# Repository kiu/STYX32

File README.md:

# STYX32
STYX32 - STM32 In-Circuit-Programming

# Connectors
STYX32 puts every programming and debug connection on the same pinout. Target boards use one of
these headers; pins 1, 3 and 5 are always 3V3, RESET (GND on D) and GND.

| Marking | Header | 1 | 2 | 3 | 4 | 5 | 6 | 7 | 8 | 9 | 10 |
|---|---|---|---|---|---|---|---|---|---|---|---|
| S32A | 2x3 serial | 3V3 | TX | RESET | RX | GND | BOOT0 | | | | |
| S32B1 | 2x3 SWD + serial | 3V3 | SWDIO | RESET | SWDCLK | GND | TX | | | | |
| S32B2 | 2x3 SWD + SWO | 3V3 | SWDIO | RESET | SWDCLK | GND | SWO | | | | |
| S32C | 2x4 SWD + SWO + serial | 3V3 | SWDIO | RESET | SWDCLK | GND | SWO | TX | RX | | |
| S32D | 2x5 ARM Cortex debug | 3V3 | SWDIO | GND | SWDCLK | GND | SWO | KEY | TDI | GND | RESET |

TX and RX are seen from the target: TX is the target's output.

## KiCad library
[lib/](lib/) has a symbol and a footprint for every connector in four variants (2.54 mm and
1.27 mm pitch, SMD and THT), named `STYX32_<connector>_2x<rows>_<pitch>_<SMD|THT>`. The symbols
look like KiCad's generic 2-row connectors, link their footprint and carry the LCSC part number.
The footprints show the marking (e.g. S32B2), a pin 1 mark and the key notch on the silkscreen,
and the pin names on F.Fab.

Every connector also comes as a card edge, `STYX32_<connector>_2x<rows>_P2.54mm_Edge`: gold
fingers on both sides of a 1.6 mm board (odd pins on top, even pins below them) that plug into a
2.54 mm edge slot socket, e.g. WingTAT ED06BGFBK / ED08BGFBK / ED10BGFBK (LCSC C5173287 / C5173288 /
C5173289, in the symbol's `Mate` field). The socket has no key: a triangle on top and a square on
the bottom mark the pin 1 end. The footprint brings the card outline on Edge.Cuts; join its two
ends to your board edge, straight across for a card sticking out of the board, or along the notch
guide on User.Drawings for a card cut into the board. The plugged socket is drawn on User.Drawings
beyond the card edge. Card edges are not part of the BOM; ENIG is fine, a bevelled edge plugs in
more easily.

The [template](lib/template/) schematic has every connector wired to global labels
(`STM_SWDIO`, `STM_SWDCLK`, `STM_SWO`, `STM_RESET`, `STM_TX`, `STM_RX`, `STM_BOOT0`, `STM_TDI`),
`+3V3` and `GND`: copy a connector with its labels into your own schematic.

1. Add `lib/STYX32.kicad_sym` and `lib/STYX32.pretty` to your symbol and footprint library tables
   (nickname `STYX32`).
2. For the 1.27 mm 3D models, set the path variable `STYX32_LIB` to the `lib` folder
   (Preferences > Configure Paths).

The whole library is generated by [lib/tools/](lib/tools/): `gen_symbols.py` (any Python),
`gen_footprints.py` (KiCad's Python) and `make_3d.py` (FreeCAD) for the 1.27 mm models.

# Files
- [main](REV_A/main/): KiCad schematic, board and gerbers
- [template](lib/template/): KiCad project showing every connector of the library
- [lib](lib/): KiCad symbol and footprint library for the connectors
- [BOM](REV_A/STYX32-bom.ods): Bill of materials [(PDF)](REV_A/STYX32-bom.pdf)
- [firmware](firmware/): STM32CubeIDE project

# Links
- [IDCto127](https://github.com/kiu/IDCto127)

# License
This project is licensed under the Creative Commons Attribution-NonCommercial 3.0 Unported (CC BY-NC 3.0) license.

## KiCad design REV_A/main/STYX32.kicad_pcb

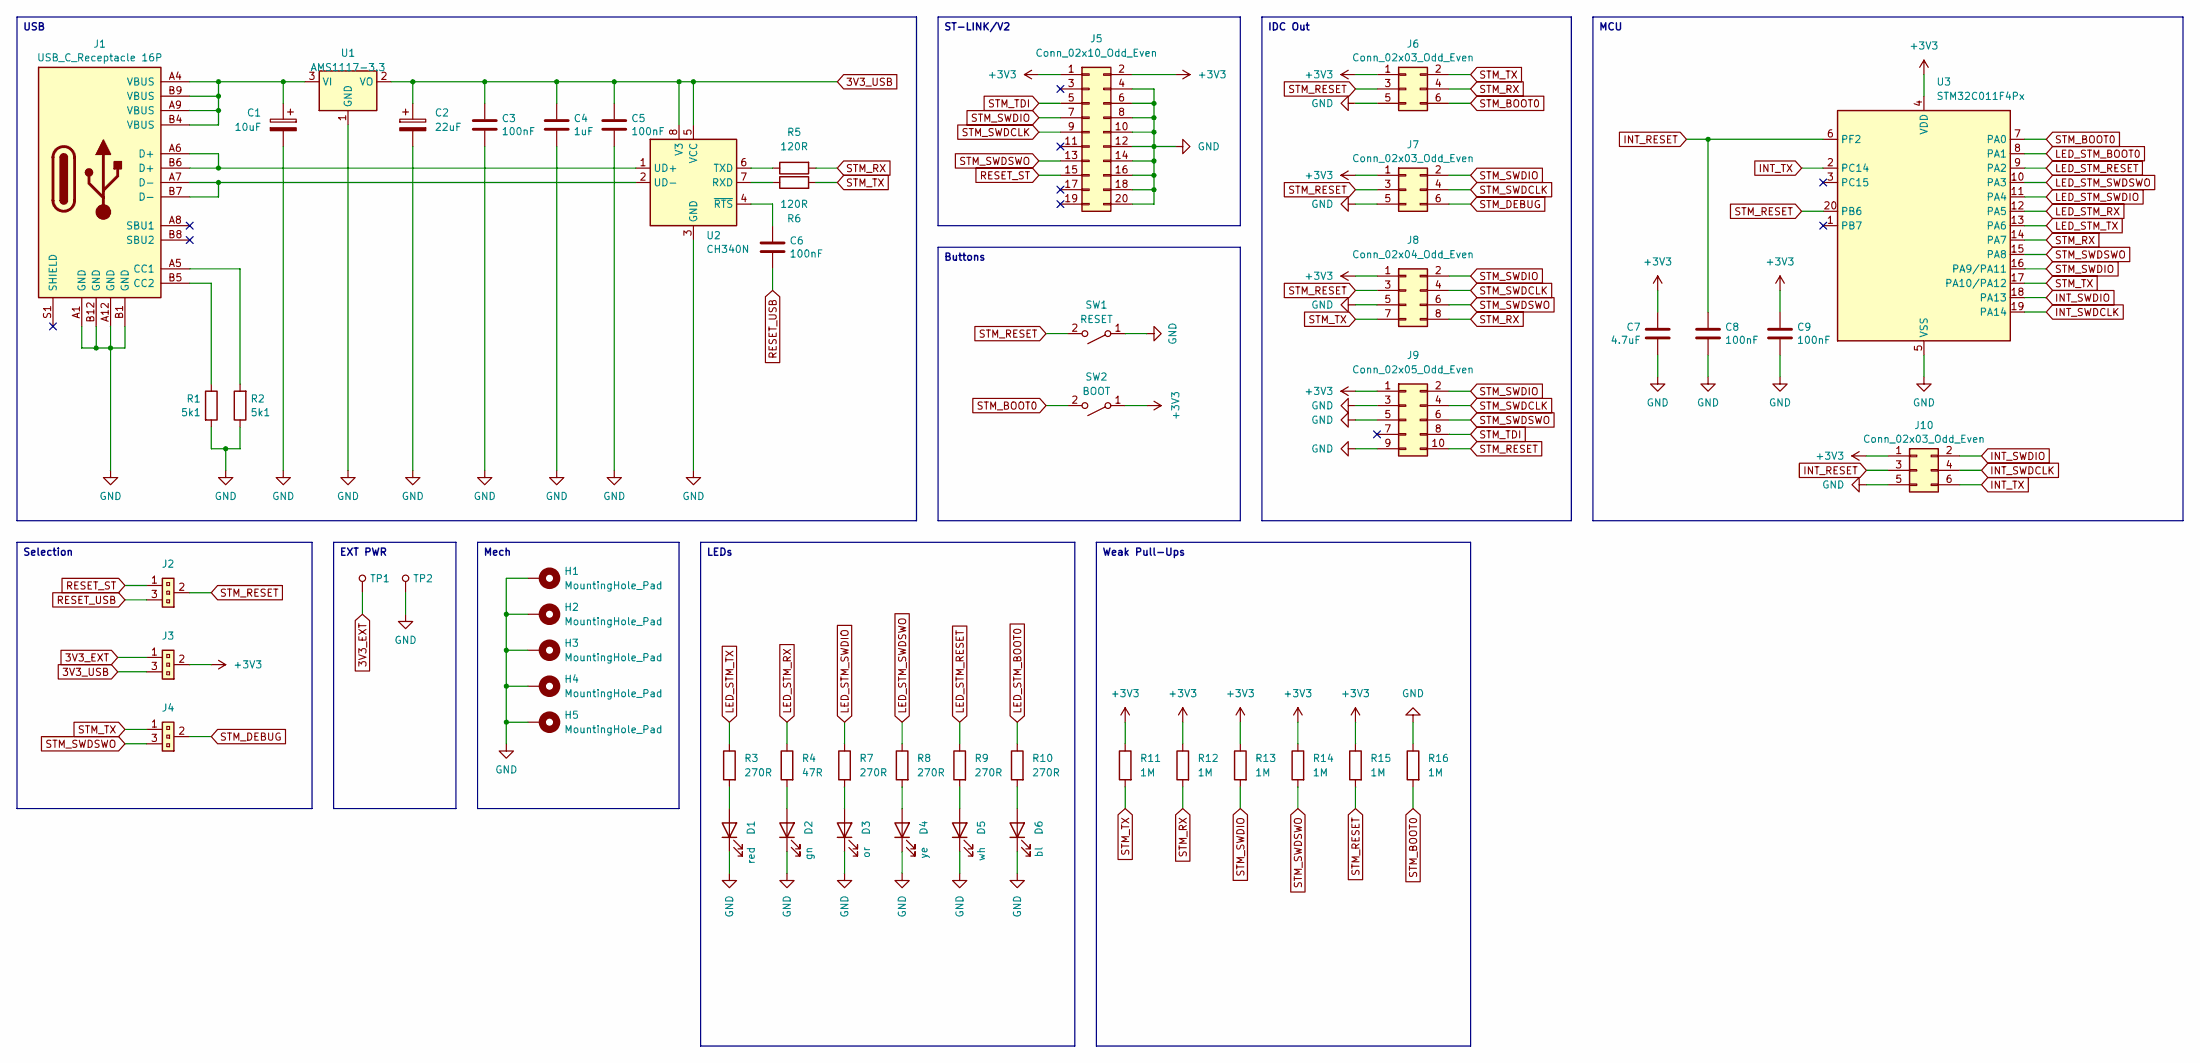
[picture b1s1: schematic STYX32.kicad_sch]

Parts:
C1: 10uF; CP_EIA-3216-18_Kemet-A; LCSC C119052
C2: 22uF; CP_EIA-3216-18_Kemet-A; LCSC C122643
C3, C5, C6, C8, C9: 100nF; C_0805_2012Metric; LCSC C49678
C4: 1uF; C_0805_2012Metric; LCSC C28323
C7: 4.7uF; C_0805_2012Metric; LCSC C98192
D1: red; LED_1206_TOGIALED TJ-S3216SWETNPLC2_REVERSE; LCSC C7545697
D2: gn; LED_1206_TOGIALED TJ-S3216SWETNPLC2_REVERSE; LCSC C7545703
D3: or; LED_1206_TOGIALED TJ-S3216SWETNPLC2_REVERSE; LCSC C7545709
D4: ye; LED_1206_TOGIALED TJ-S3216SWETNPLC2_REVERSE; LCSC C7545699
D5: wh; LED_1206_TOGIALED TJ-S3216SWETNPLC2_REVERSE; LCSC C7545707
D6: bl; LED_1206_TOGIALED TJ-S3216SWETNPLC2_REVERSE; LCSC C7545701
H1, H2, H3, H4, H5: MountingHole_Pad; MountingHole_3.2mm_M3_DIN965_Pad
J1: USB_C_Receptacle 16P; USB_C_Receptacle_Korean_Hroparts_Elec_TYPE-C-31-M-12; LCSC C165948
J2, J3, J4: 1x03_Jumper; PinHeader_1x03_P2.54mm_Vertical; LCSC C6332196
J5: Conn_02x10_Odd_Even; IDC-Header_2x10_P2.54mm_Vertical; LCSC C93700
J6, J7: Conn_02x03_Odd_Even; IDC-Header_2x03_P2.54mm_Vertical; LCSC C492441
J8: Conn_02x04_Odd_Even; IDC-Header_2x04_P2.54mm_Vertical; LCSC C17179451
J9: Conn_02x05_Odd_Even; IDC-Header_2x05_P2.54mm_Vertical; LCSC C5665
J10: Conn_02x03_Odd_Even; IDC-Header_2x03_P1.27mm_Vertical_SMD; LCSC C42372553
R1, R2: 5k1; R_0805_2012Metric; LCSC C27834
R3, R7, R8, R9, R10: 270R; R_0805_2012Metric; LCSC C2907313
R4: 47R; R_0805_2012Metric; LCSC C2907331
R5, R6: 120R; R_0805_2012Metric; LCSC C17437
R11, R12, R13, R14, R15, R16: 1M; R_0805_2012Metric; LCSC C2907302
SW1: RESET; SW_PUSH-12mm; LCSC C2843931
SW2: BOOT; SW_PUSH-12mm; LCSC C2843931
TP1, TP2: 5011; TestPoint_Keystone_5010-5014_Multipurpose; MPN 5011; Digi-Key_PN 36-5011-ND
U1: AMS1117-3.3; SOT-223-3_TabPin2; LCSC C347222
U2: CH340N; SOP-8_3.9x4.9mm_P1.27mm; LCSC C2977777
U3: STM32C011F4Px; TSSOP-20_4.4x6.5mm_P0.65mm; LCSC C7373263

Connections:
3V3_EXT: J3.1, TP1.1
3V3_USB: C2.1, C3.1, C4.1, C5.1, J3.3, U1.2 (VO), U2.5 (VCC), U2.8 (V3)
+3V3: C7.1, C9.1, J3.2, J5.1, J5.2, J6.1, J7.1, J8.1, J9.1, J10.1, R11.1, R12.1, R13.1, R14.1, R15.1, SW2.1 (A), U3.4 (VDD)
GND: C1.2, C2.2, C3.2, C4.2, C5.2, C7.2, C8.2, C9.2, D1.1 (K), D2.1 (K), D3.1 (K), D4.1 (K), D5.1 (K), D6.1 (K), H1.1, H2.1, H3.1, H4.1, H5.1, J1.A1 (GND), J1.A12 (GND), J1.B1 (GND), J1.B12 (GND), J5.4, J5.6, J5.8, J5.10, J5.12, J5.14, J5.16, J5.18, J5.20, J6.5, J7.5, J8.5, J9.3, J9.5, J9.9, J10.5, R1.2, R2.1, R16.1, SW1.1 (A), TP2.1, U1.1 (GND), U2.3 (GND), U3.5 (VSS)
INT_RESET: C8.1, J10.3, U3.6 (PF2)
INT_SWDCLK: J10.4, U3.19 (PA14)
INT_SWDIO: J10.2, U3.18 (PA13)
INT_TX: J10.6, U3.2 (PC14)
LED_STM_BOOT0: R10.1, U3.8 (PA1)
LED_STM_RESET: R9.1, U3.9 (PA2)
LED_STM_RX: R4.1, U3.12 (PA5)
LED_STM_SWDIO: R7.1, U3.11 (PA4)
LED_STM_SWDSWO: R8.1, U3.10 (PA3)
LED_STM_TX: R3.1, U3.13 (PA6)
unnamed: D1.2 (A), R3.2
unnamed: D2.2 (A), R4.2
unnamed: D3.2 (A), R7.2
unnamed: D4.2 (A), R8.2
unnamed: D5.2 (A), R9.2
unnamed: D6.2 (A), R10.2
unnamed: J1.A5 (CC1), R2.2
unnamed: J1.B5 (CC2), R1.1
unnamed: C1.1, J1.A4 (VBUS), J1.A9 (VBUS), J1.B4 (VBUS), J1.B9 (VBUS), U1.3 (VI)
unnamed: R6.1, U2.7 (RXD)
unnamed: R5.1, U2.6 (TXD)
unnamed: J1.A6 (D+), J1.B6 (D+), U2.1 (UD+)
unnamed: J1.A7 (D-), J1.B7 (D-), U2.2 (UD-)
unnamed: C6.1, U2.4 (~RTS)
RESET_ST: J2.1, J5.15
RESET_USB: C6.2, J2.3
STM_BOOT0: J6.6, R16.2, SW2.2 (B), U3.7 (PA0)
STM_DEBUG: J4.2, J7.6
STM_RESET: J2.2, J6.3, J7.3, J8.3, J9.10, R15.2, SW1.2 (B), U3.20 (PB6)
STM_RX: J6.4, J8.8, R5.2, R12.2, U3.14 (PA7)
STM_SWDCLK: J5.9, J7.4, J8.4, J9.4
STM_SWDIO: J5.7, J7.2, J8.2, J9.2, R13.2, U3.16 (PA9/PA11)
STM_SWDSWO: J4.3, J5.13, J8.6, J9.6, R14.2, U3.15 (PA8)
STM_TDI: J5.5, J9.8
STM_TX: J4.1, J6.2, J8.7, R6.2, R11.2, U3.17 (PA10/PA12)

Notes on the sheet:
Weak Pull-Ups
ST-LINK/V2
Mech
Buttons
EXT PWR
LEDs
USB
IDC Out
MCU
Selection

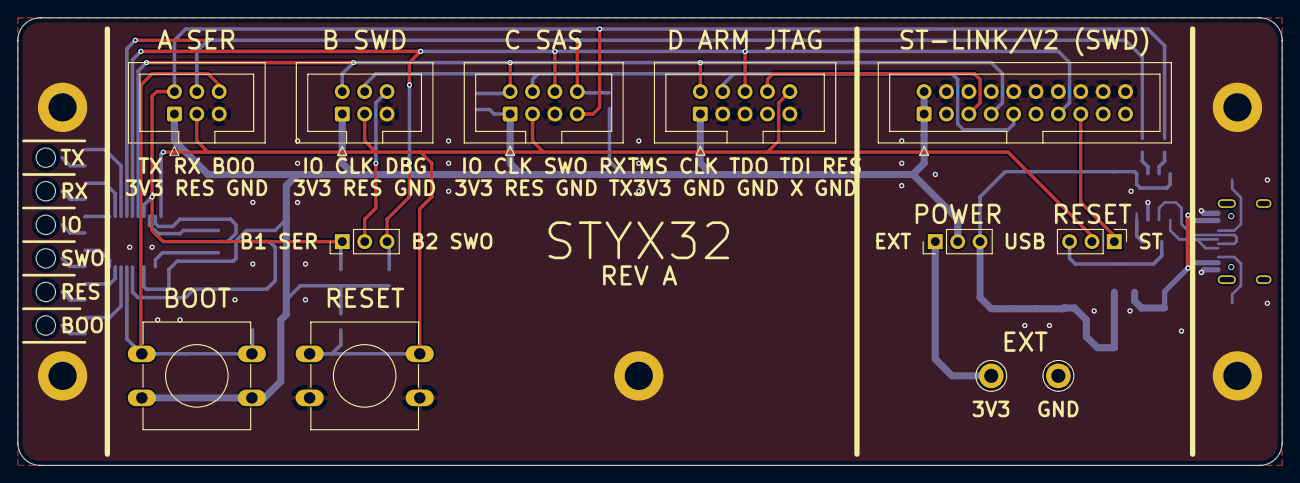
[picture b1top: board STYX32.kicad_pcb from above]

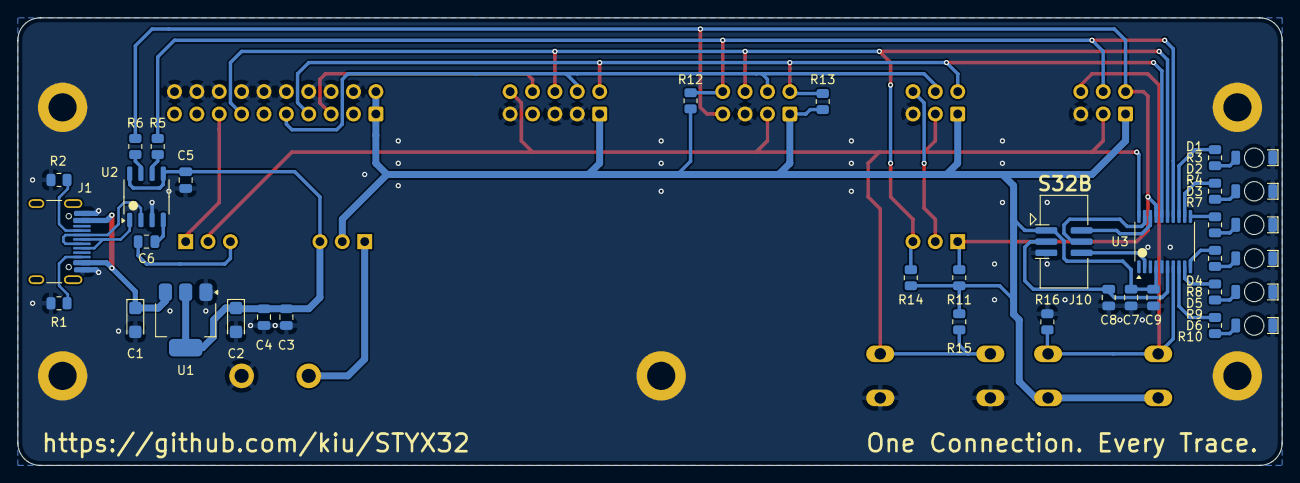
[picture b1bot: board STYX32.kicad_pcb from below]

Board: 2 copper layers, 143.5 x 50.8 mm, 53 parts (36 on the bottom side), 39 nets.

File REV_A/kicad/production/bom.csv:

Designator,Footprint,Quantity,Value,LCSC Part #
C1,CP_EIA-3216-18_Kemet-A,1,10uF,C119052
C2,CP_EIA-3216-18_Kemet-A,1,22uF,C122643
"C3, C5, C6, C8, C9",0805,5,100nF,C49678
C4,0805,1,1uF,C28323
C7,0805,1,4.7uF,C98192
D1,LED_1206_TOGIALED TJ-S3216SWETNPLC2_REVERSE,1,red,C7545697
D2,LED_1206_TOGIALED TJ-S3216SWETNPLC2_REVERSE,1,gn,C7545703
D3,LED_1206_TOGIALED TJ-S3216SWETNPLC2_REVERSE,1,or,C7545709
D4,LED_1206_TOGIALED TJ-S3216SWETNPLC2_REVERSE,1,ye,C7545699
D5,LED_1206_TOGIALED TJ-S3216SWETNPLC2_REVERSE,1,wh,C7545707
D6,LED_1206_TOGIALED TJ-S3216SWETNPLC2_REVERSE,1,bl,C7545701
J1,USB_C_Receptacle_Korean_Hroparts_Elec_TYPE-C-31-M-12,1,USB_C_Receptacle 16P,C165948
J10,IDC-Header_2x03_P1.27mm_Vertical_SMD,1,Conn_02x03_Odd_Even,C42372553
"J2, J3, J4",PinHeader_1x03_P2.54mm_Vertical,3,1x03_Jumper,C6332196
J5,IDC-Header_2x10_P2.54mm_Vertical,1,Conn_02x10_Odd_Even,C93700
"J6, J7",IDC-Header_2x03_P2.54mm_Vertical,2,Conn_02x03_Odd_Even,C492441
J8,IDC-Header_2x04_P2.54mm_Vertical,1,Conn_02x04_Odd_Even,C17179451
J9,IDC-Header_2x05_P2.54mm_Vertical,1,Conn_02x05_Odd_Even,C5665
"R1, R2",0805,2,5k1,C27834
"R10, R3, R7, R8, R9",0805,5,270R,C2907313
"R11, R12, R13, R14, R15, R16",0805,6,1M,C2907302
R4,0805,1,47R,C2907331
"R5, R6",0805,2,120R,C17437
SW1,SW_PUSH-12mm,1,RESET,C2843931
SW2,SW_PUSH-12mm,1,BOOT,C2843931
TP1,TestPoint_Keystone_5010-5014_Multipurpose,1,5011,C2906765
TP2,TestPoint_Keystone_5010-5014_Multipurpose,1,5011,C238127
U1,SOT-223-3_TabPin2,1,AMS1117-3.3,C347222
U2,SOP-8_3.9x4.9mm_P1.27mm,1,CH340N,C2977777
U3,TSSOP-20_4.4x6.5mm_P0.65mm,1,STM32C011F4Px,C7373263

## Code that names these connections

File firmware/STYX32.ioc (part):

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Mcu.Name=STM32C011F(4-6)Px
Mcu.Package=TSSOP20
Mcu.UserName=STM32C011F4Px
PA0.GPIOParameters=GPIO_Label
PA0.GPIO_Label=STM_BOOT0
PA0.Signal=GPXTI0
PA1.GPIOParameters=GPIO_Label
PA1.GPIO_Label=LED_STM_BOOT0
PA1.Signal=GPIO_Output
PA11\ [PA9].GPIOParameters=GPIO_Label,GPIO_ModeDefaultEXTI
PA11\ [PA9].GPIO_Label=STM_SWDIO
PA11\ [PA9].GPIO_ModeDefaultEXTI=GPIO_MODE_IT_FALLING
PA11\ [PA9].Signal=GPXTI11
PA12\ [PA10].GPIOParameters=GPIO_PuPd,GPIO_Label,GPIO_ModeDefaultEXTI
PA12\ [PA10].GPIO_Label=STM_TX
PA12\ [PA10].GPIO_ModeDefaultEXTI=GPIO_MODE_IT_FALLING
PA12\ [PA10].GPIO_PuPd=GPIO_PULLUP
PA12\ [PA10].Signal=GPXTI12
PA13.Mode=Serial_Wire
PA13.Signal=DEBUG_SWDIO
PA14-BOOT0.Mode=Serial_Wire
PA14-BOOT0.Signal=DEBUG_SWCLK
PA2.GPIOParameters=GPIO_Label
PA2.GPIO_Label=LED_STM_RESET
PA2.Signal=GPIO_Output
PA3.GPIOParameters=GPIO_Label
PA3.GPIO_Label=LED_STM_SWDSWO
PA3.Signal=GPIO_Output
PA4.GPIOParameters=GPIO_Label
PA4.GPIO_Label=LED_STM_SWDIO
PA4.Signal=GPIO_Output
PA5.GPIOParameters=GPIO_Label
PA5.GPIO_Label=LED_STM_RX
PA5.Signal=GPIO_Output
PA6.GPIOParameters=GPIO_Label
PA6.GPIO_Label=LED_STM_TX
PA6.Signal=GPIO_Output
PA7.GPIOParameters=GPIO_PuPd,GPIO_Label,GPIO_ModeDefaultEXTI
PA7.GPIO_Label=STM_RX
PA7.GPIO_ModeDefaultEXTI=GPIO_MODE_IT_FALLING
PA7.GPIO_PuPd=GPIO_PULLUP
PA7.Signal=GPXTI7
PA8.GPIOParameters=GPIO_Label,GPIO_ModeDefaultEXTI
PA8.GPIO_Label=STM_SWDSWO
PA8.GPIO_ModeDefaultEXTI=GPIO_MODE_IT_FALLING
PA8.Signal=GPXTI8
PB6.GPIOParameters=GPIO_Label,GPIO_ModeDefaultEXTI
PB6.GPIO_Label=STM_RESET
PB6.GPIO_ModeDefaultEXTI=GPIO_MODE_IT_FALLING
PB6.Signal=GPXTI6
PB7.Mode=Asynchronous
PB7.Signal=USART1_RX
PC14-OSCX_IN\ (PC14).Mode=Asynchronous
PC14-OSCX_IN\ (PC14).Signal=USART1_TX
RCC.HSE_VALUE=8000000
RCC.SYSCLKFreq_VALUE=12000000
board=custom
